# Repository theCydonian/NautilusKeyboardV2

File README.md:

# NautilusKeyboardV2
WIP Wireless 44% keyboard

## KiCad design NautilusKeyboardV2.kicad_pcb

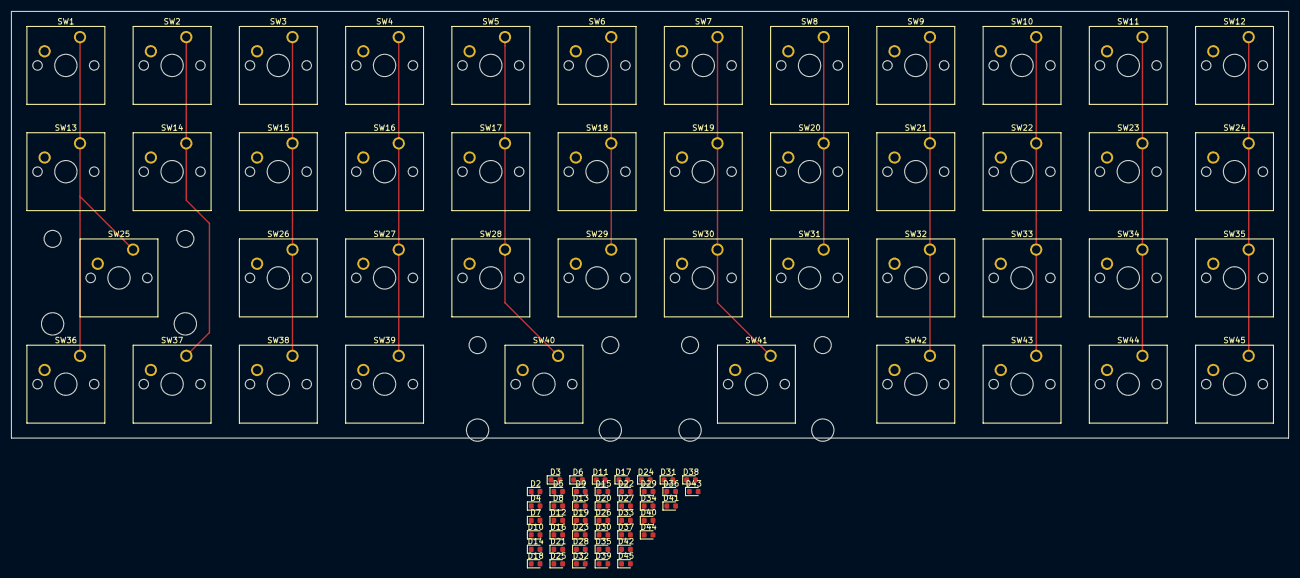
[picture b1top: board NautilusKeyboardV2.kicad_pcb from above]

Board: 2 copper layers, 229.0 x 76.5 mm, 90 parts (1 on the bottom side), 61 nets.

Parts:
D1, D2, D3, D4, D5, D6, D7, D8, D9, D10, D11, D12, D13, D14, D15, D16, D17, D18, D19, D20, D21, D22, D23, D24, D25, D26, D27, D28, D29, D30, D31, D32, D33, D34, D35, D36, D37, D38, D39, D40, D41, D42, D43, D44, D45: D_Small_ALT; D_0603_1608Metric
SW1, SW2, SW3, SW4, SW5, SW6, SW7, SW8, SW9, SW10, SW11, SW12, SW13, SW14, SW15, SW16, SW17, SW18, SW19, SW20, SW21, SW22, SW23, SW24, SW26, SW27, SW28, SW29, SW30, SW31, SW32, SW33, SW34, SW35, SW36, SW37, SW38, SW39, SW42, SW43, SW44, SW45: SW_Push; SW_Cherry_MX_1.00u_PCB
SW25, SW40, SW41: SW_Push; SW_Cherry_MX_2.00u_PCB

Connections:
unnamed: D1.2, SW1.2
unnamed: D2.2, SW2.2
unnamed: D3.2, SW3.2
unnamed: D4.2, SW4.2
unnamed: D5.2, SW5.2
unnamed: D6.2, SW6.2
unnamed: D7.2, SW7.2
unnamed: D8.2, SW8.2
unnamed: D9.2, SW9.2
unnamed: D10.2, SW10.2
unnamed: D11.2, SW11.2
unnamed: D12.2, SW12.2
unnamed: D13.2, SW13.2
unnamed: D14.2, SW14.2
unnamed: D15.2, SW15.2
unnamed: D16.2, SW16.2
unnamed: D17.2, SW17.2
unnamed: D18.2, SW18.2
unnamed: D19.2, SW19.2
unnamed: D20.2, SW20.2
unnamed: D21.2, SW21.2
unnamed: D22.2, SW22.2
unnamed: D23.2, SW23.2
unnamed: D24.2, SW24.2
unnamed: D25.2, SW25.2
unnamed: D26.2, SW26.2
unnamed: D27.2, SW27.2
unnamed: D28.2, SW28.2
unnamed: D29.2, SW29.2
unnamed: D30.2, SW30.2
unnamed: D31.2, SW31.2
unnamed: D32.2, SW32.2
unnamed: D33.2, SW33.2
unnamed: D34.2, SW34.2
unnamed: D35.2, SW35.2
unnamed: D36.2, SW36.2
unnamed: D37.2, SW37.2
unnamed: D38.2, SW38.2
unnamed: D39.2, SW39.2
unnamed: D40.2, SW40.2
unnamed: D41.2, SW41.2
unnamed: D42.2, SW42.2
unnamed: D43.2, SW43.2
unnamed: D44.2, SW44.2
unnamed: D45.2, SW45.2
c0: SW1.1, SW13.1, SW25.1, SW36.1
c1: SW2.1, SW14.1, SW37.1
c2: SW3.1, SW15.1, SW26.1, SW38.1
c3: SW4.1, SW16.1, SW27.1, SW39.1
c4: SW5.1, SW17.1, SW28.1, SW40.1
c5: SW6.1, SW18.1, SW29.1
c6: SW7.1, SW19.1, SW30.1, SW41.1
c7: SW8.1, SW20.1, SW31.1
c8: SW9.1, SW21.1, SW32.1, SW42.1
c9: SW10.1, SW22.1, SW33.1, SW43.1
c10: SW11.1, SW23.1, SW34.1, SW44.1
c11: SW12.1, SW24.1, SW35.1, SW45.1
r0: D1.1, D2.1, D3.1, D4.1, D5.1, D6.1, D7.1, D8.1, D9.1, D10.1, D11.1, D12.1
r1: D13.1, D14.1, D15.1, D16.1, D17.1, D18.1, D19.1, D20.1, D21.1, D22.1, D23.1, D24.1
r2: D25.1, D26.1, D27.1, D28.1, D29.1, D30.1, D31.1, D32.1, D33.1, D34.1, D35.1
r3: D36.1, D37.1, D38.1, D39.1, D40.1, D41.1, D42.1, D43.1, D44.1, D45.1

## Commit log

2022-03-28 upload github
